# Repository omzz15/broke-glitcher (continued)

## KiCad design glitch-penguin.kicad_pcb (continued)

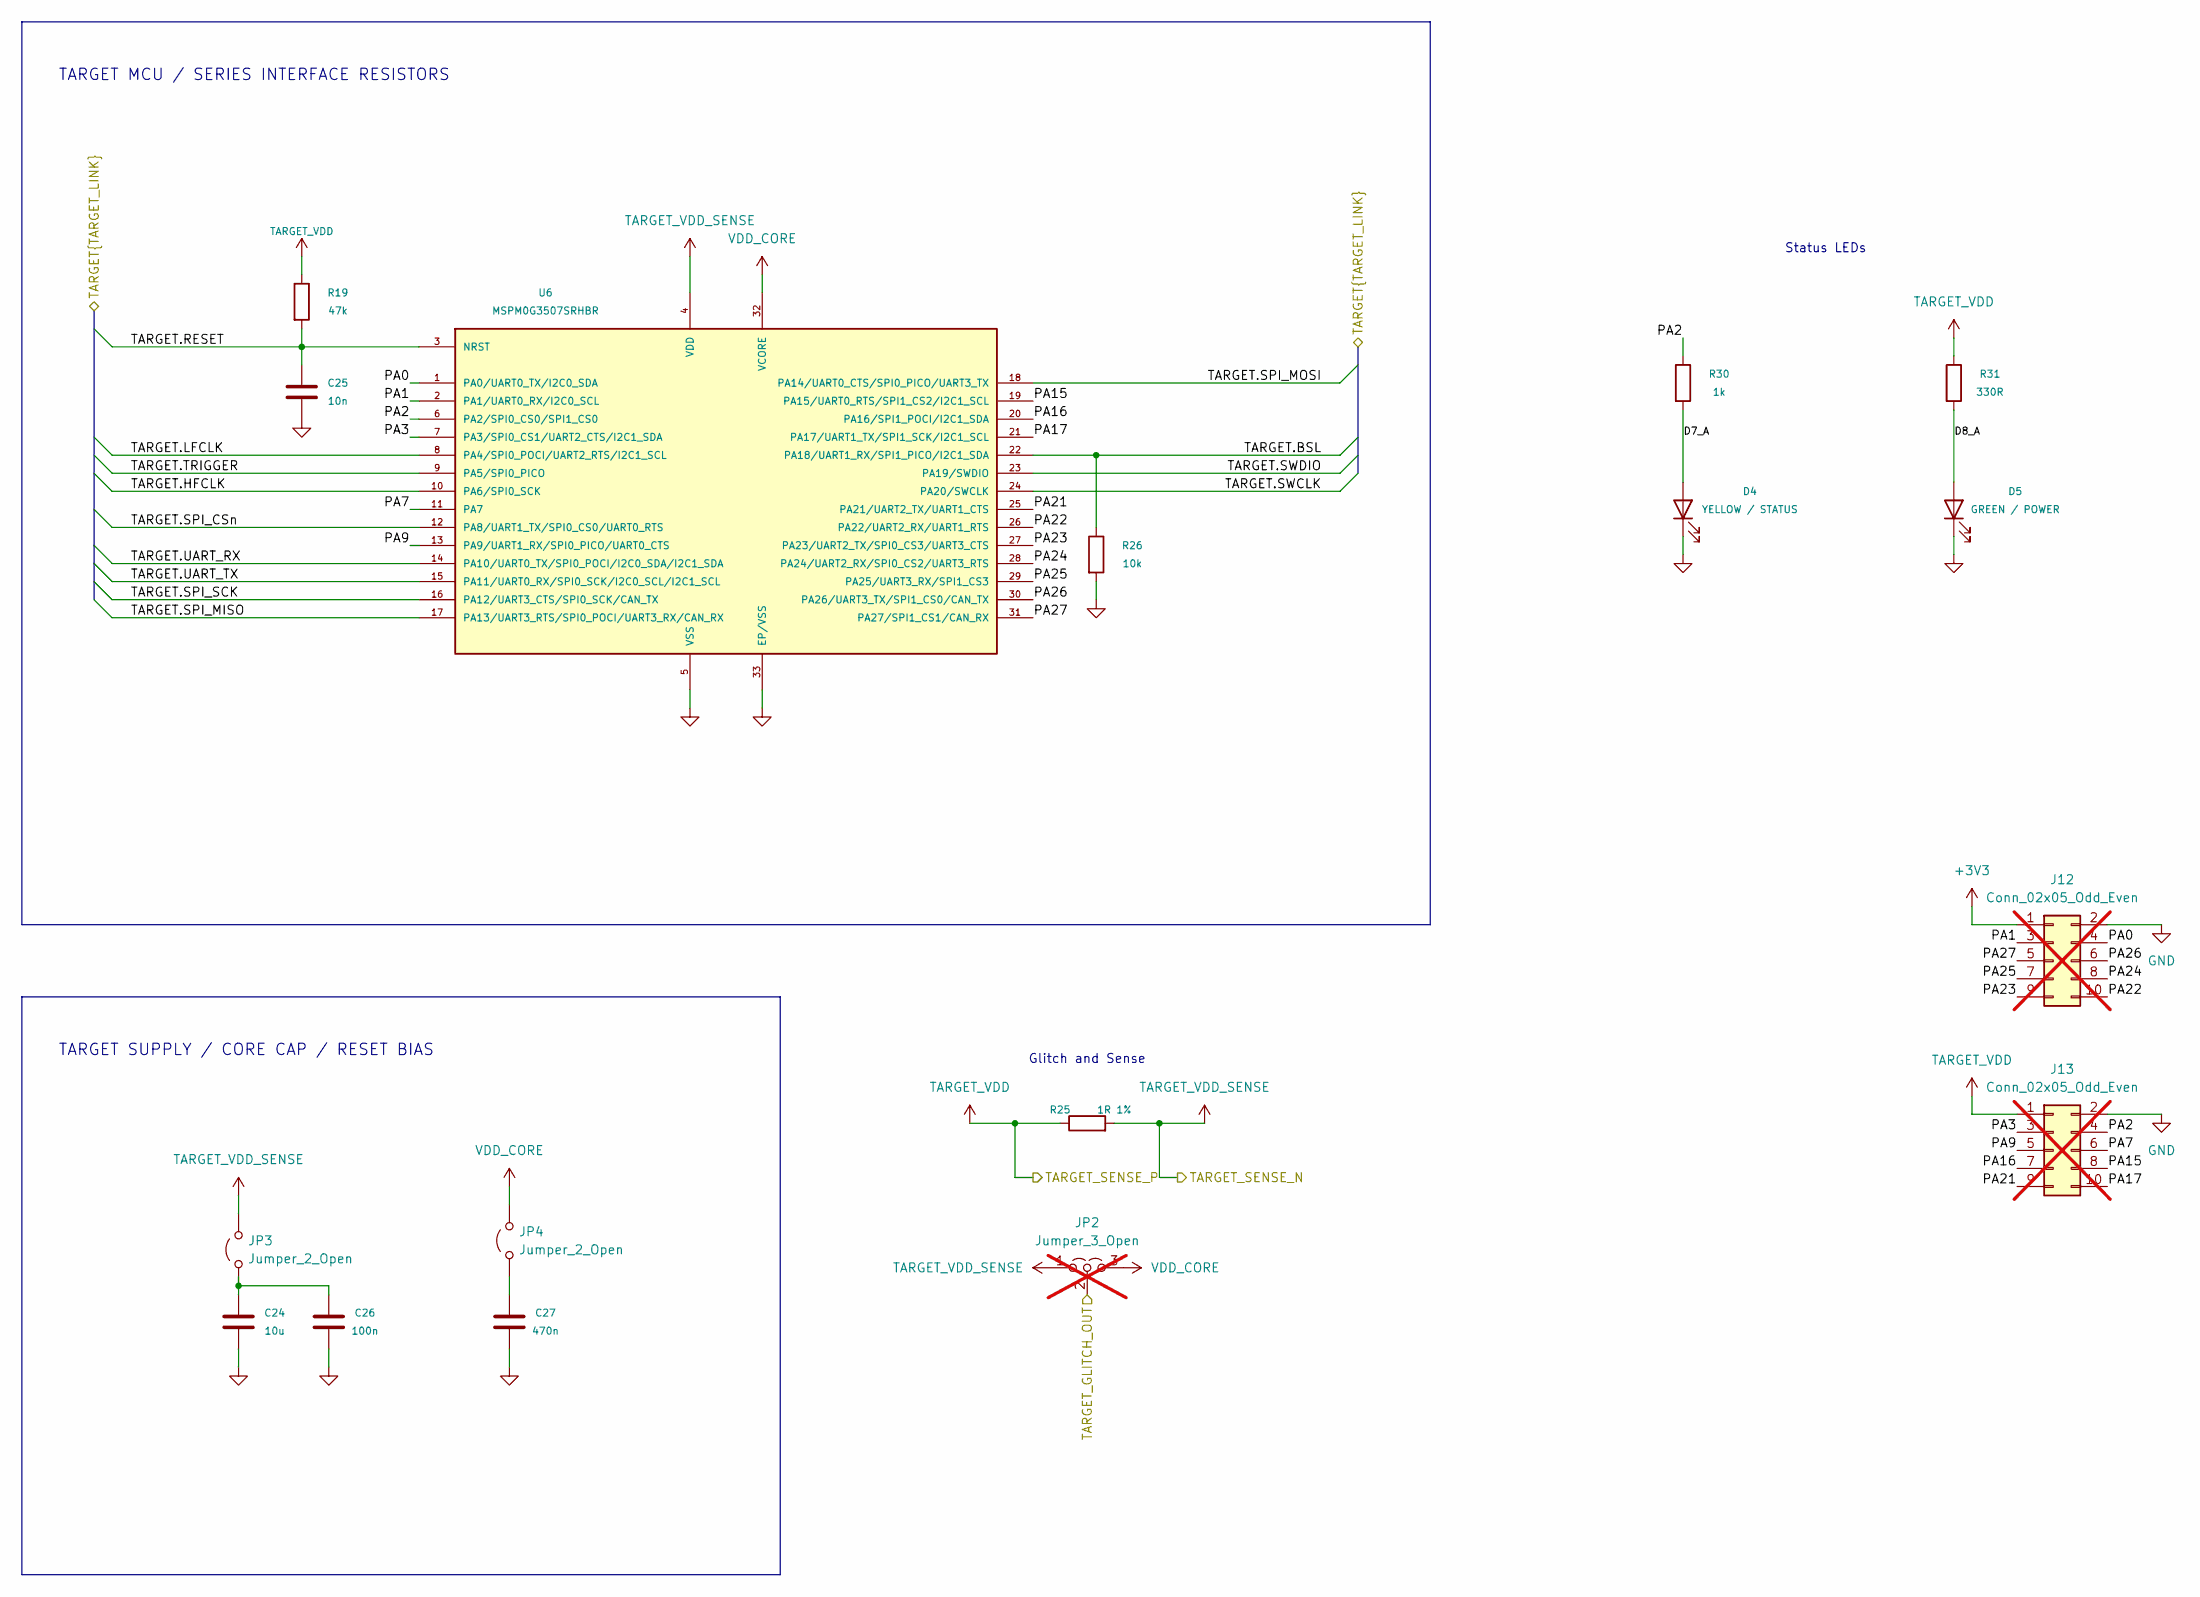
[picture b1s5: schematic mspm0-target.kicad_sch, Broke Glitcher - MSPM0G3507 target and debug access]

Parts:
C24: 10u; C_0805_2012Metric; MPN CL21A106KAYNNNE; LCSC Part # C15850
C25: 10n; C_0402_1005Metric; Tolerance ±10%; Voltage Rating 50 V; MPN CL05B103KB5NNNC; LCSC Part # C15195
C26: 100n; C_0402_1005Metric; Tolerance ±10%; Voltage Rating 16 V; MPN CL05B104KO5NNNC; LCSC Part # C1525
C27: 470n; C_0603_1608Metric; MPN CL10B474KA8NNNC; LCSC Part # C1623
D4: YELLOW / STATUS; LED_0603_1608Metric; MPN KT-0603Y; LCSC Part # C2287
D5: GREEN / POWER; LED_0603_1608Metric; MPN KT-0603G; LCSC Part # C12624
J12, J13: Conn_02x05_Odd_Even; PinHeader_2x05_P2.54mm_Vertical; not fitted
JP2: Jumper_3_Open; PinHeader_1x03_P2.54mm_Vertical; not fitted
JP3, JP4: Jumper_2_Open; SolderJumper-2_P1.3mm_Open_TrianglePad1.0x1.5mm
R19: 47k; R_0402_1005Metric; Tolerance ±1%; Voltage Rating 50 V; MPN 0402WGF4702TCE; LCSC Part # C25792
R25: 1R 1%; R_1206_3216Metric; MPN RC1206FR-071RL; LCSC Part # C137355
R26: 10k; R_0402_1005Metric; Tolerance ±1%; Voltage Rating 50 V; MPN 0402WGF1002TCE; LCSC Part # C25744
R30: 1k; R_0402_1005Metric; Tolerance ±1%; Voltage Rating 50 V; MPN 0402WGF1001TCE; LCSC Part # C11702
R31: 330R; R_0402_1005Metric; Tolerance ±1%; Voltage Rating 50 V; MPN 0402WGF3300TCE; LCSC Part # C25104
U6: MSPM0G3507SRHBR; Texas_RHB0032E_VQFN-32-1EP_5x5mm_P0.5mm_EP3.45x3.45mm_Therm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; MPN MSPM0G3507SRHBR; LCSC Part # C20618748

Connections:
+3V3: J12.1; also elsewhere on the board
/Breakaway interface/LINK_GPIO16: U6.17 (PA13/UART3_RTS/SPI0_POCI/UART3_RX/CAN_RX); also elsewhere on the board
/Breakaway interface/LINK_GPIO18: U6.16 (PA12/UART3_CTS/SPI0_SCK/CAN_TX); also elsewhere on the board
/Breakaway interface/LINK_GPIO19: U6.18 (PA14/UART0_CTS/SPI0_PICO/UART3_TX); also elsewhere on the board
/Breakaway interface/LINK_GPIO20: U6.15 (PA11/UART0_RX/SPI0_SCK/I2C0_SCL/I2C1_SCL); also elsewhere on the board
/Breakaway interface/LINK_GPIO21: U6.14 (PA10/UART0_TX/SPI0_POCI/I2C0_SDA/I2C1_S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); also elsewhere on the board
/Breakaway interface/LINK_GPIO22: U6.12 (PA8/UART1_TX/SPI0_CS0/UART0_RTS); also elsewhere on the board
/Breakaway interface/LINK_GPIO23: U6.10 (PA6/SPI0_SCK); also elsewhere on the board
/Breakaway interface/LINK_GPIO24: U6.9 (PA5/SPI0_PICO); also elsewhere on the board
/Breakaway interface/LINK_GPIO25: U6.8 (PA4/SPI0_POCI/UART2_RTS/I2C1_SCL); also elsewhere on the board
/Breakaway interface/LINK_GPIO26: C25.1, R19.2, U6.3 (NRST); also elsewhere on the board
/Breakaway interface/LINK_GPIO27: R26.1, U6.22 (PA18/UART1_RX/SPI1_PICO/I2C1_SDA); also elsewhere on the board
/Breakaway interface/LINK_GPIO28: U6.23 (PA19/SWDIO); also elsewhere on the board
/Breakaway interface/LINK_GPIO29: U6.24 (PA20/SWCLK); also elsewhere on the board
/Breakaway interface/TARGET_GLITCH_OUT: JP2.2 (C); also elsewhere on the board
/MSPM0G3507 target and debug access/D7_A: D4.2 (A), R30.2
/MSPM0G3507 target and debug access/D8_A: D5.2 (A), R31.2
/MSPM0G3507 target and debug access/PA0: J12.4, U6.1 (PA0/UART0_TX/I2C0_SDA)
/MSPM0G3507 target and debug access/PA1: J12.3, U6.2 (PA1/UART0_RX/I2C0_SCL)
/MSPM0G3507 target and debug access/PA2: J13.4, R30.1, U6.6 (PA2/SPI0_CS0/SPI1_CS0)
/MSPM0G3507 target and debug access/PA3: J13.3, U6.7 (PA3/SPI0_CS1/UART2_CTS/I2C1_SDA)
/MSPM0G3507 target and debug access/PA7: J13.6, U6.11 (PA7)
/MSPM0G3507 target and debug access/PA9: J13.5, U6.13 (PA9/UART1_RX/SPI0_PICO/UART0_CTS)
/MSPM0G3507 target and debug access/PA15: J13.8, U6.19 (PA15/UART0_RTS/SPI1_CS2/I2C1_SCL)
/MSPM0G3507 target and debug access/PA16: J13.7, U6.20 (PA16/SPI1_POCI/I2C1_SDA)
/MSPM0G3507 target and debug access/PA17: J13.10, U6.21 (PA17/UART1_TX/SPI1_SCK/I2C1_SCL)
/MSPM0G3507 target and debug access/PA21: J13.9, U6.25 (PA21/UART2_TX/UART1_CTS)
/MSPM0G3507 target and debug access/PA22: J12.10, U6.26 (PA22/UART2_RX/UART1_RTS)
/MSPM0G3507 target and debug access/PA23: J12.9, U6.27 (PA23/UART2_TX/SPI0_CS3/UART3_CTS)
/MSPM0G3507 target and debug access/PA24: J12.8, U6.28 (PA24/UART2_RX/SPI0_CS2/UART3_RTS)
/MSPM0G3507 target and debug access/PA25: J12.7, U6.29 (PA25/UART3_RX/SPI1_CS3)
/MSPM0G3507 target and debug access/PA26: J12.6, U6.30 (PA26/UART3_TX/SPI1_CS0/CAN_TX)
/MSPM0G3507 target and debug access/PA27: J12.5, U6.31 (PA27/SPI1_CS1/CAN_RX)
GND: C24.2, C25.2, C26.2, C27.2, D4.1 (K), D5.1 (K), J12.2, J13.2, R26.2, U6.5 (VSS), U6.33 (EP/VSS); also elsewhere on the board
unnamed: C24.1, C26.1, JP3.1 (A)
unnamed: C27.1, JP4.1 (A)
TARGET_VDD: J13.1, R19.1, R25.1, R31.1; also elsewhere on the board
TARGET_VDD_SENSE: JP2.1 (A), JP3.2 (B), R25.2, U6.4 (VDD); also elsewhere on the board
VDD_CORE: JP2.3 (B), JP4.2 (B), U6.32 (VCORE)

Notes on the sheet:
TARGET SUPPLY / CORE CAP / RESET BIAS
TARGET MCU / SERIES INTERFACE RESISTORS
Glitch and Sense
Status LEDs

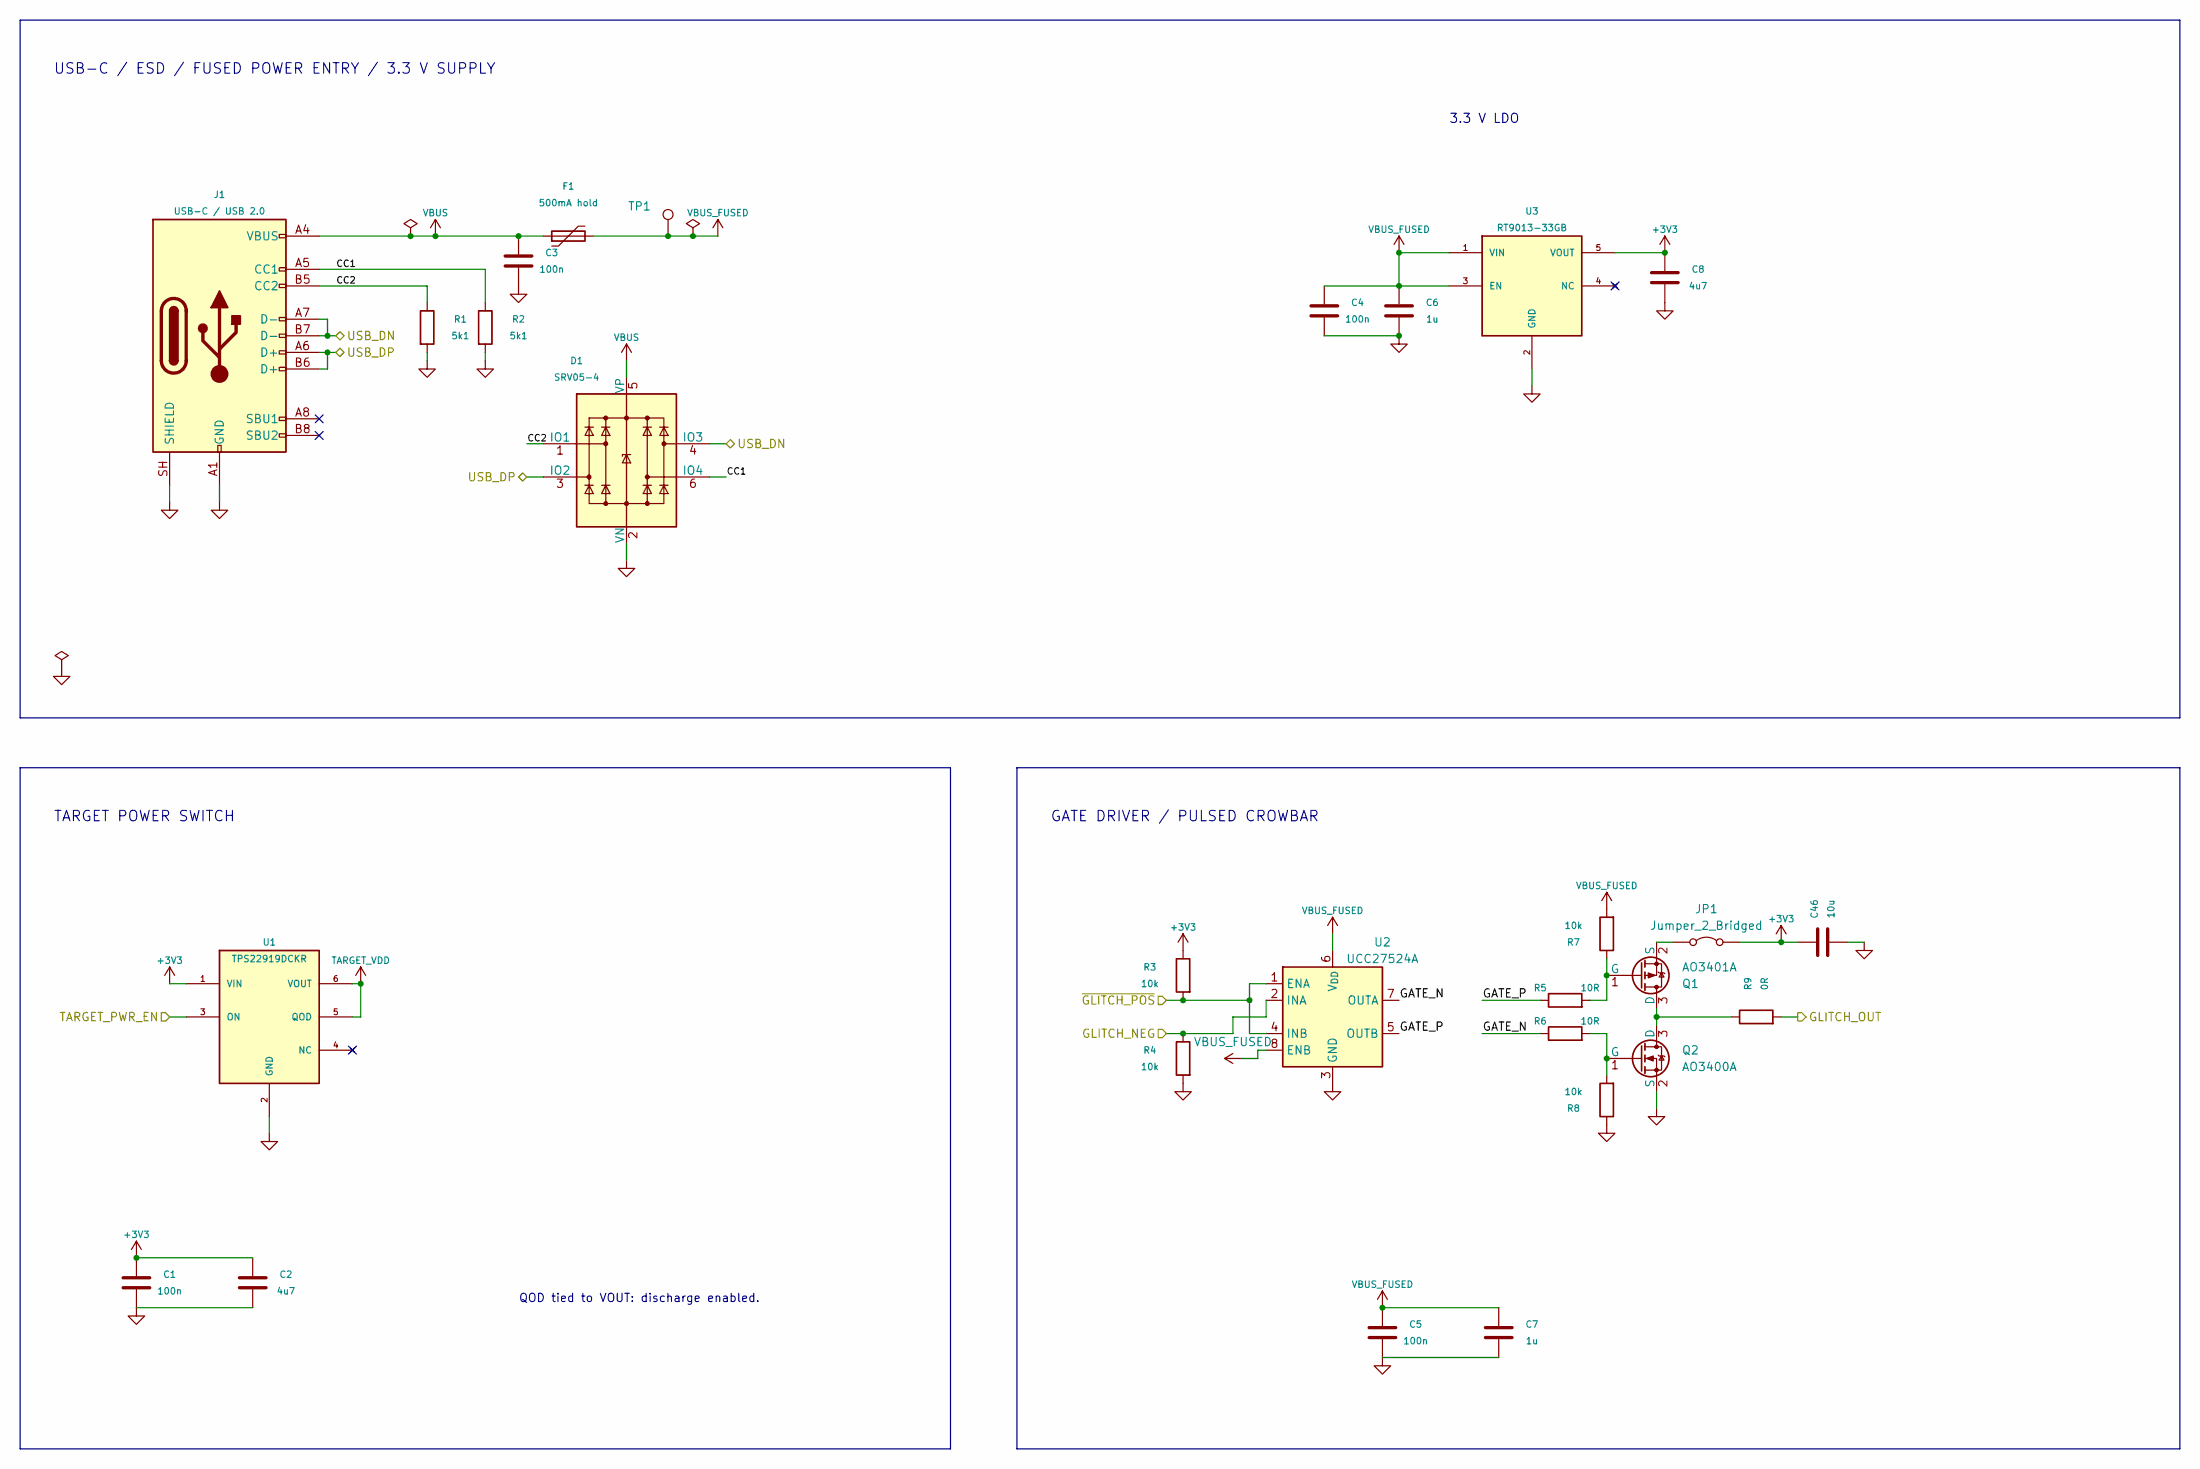
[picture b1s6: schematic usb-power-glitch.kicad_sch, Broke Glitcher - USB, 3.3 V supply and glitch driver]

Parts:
C1, C3, C4, C5: 100n; C_0402_1005Metric; Tolerance ±10%; Voltage Rating 16 V; MPN CL05B104KO5NNNC; LCSC Part # C1525
C2, C8: 4u7; C_0603_1608Metric; MPN CL10A475KP8NNNC; LCSC Part # C1705
C6, C7: 1u; C_0603_1608Metric; MPN CL10A105KB8NNNC; LCSC Part # C15849
C46: 10u; C_0805_2012Metric; MPN CL21A106KAYNNNE; LCSC Part # C15850
D1: SRV05-4; SOT-23-6; MPN SRV05-4; LCSC Part # C384887
F1: 500mA hold; Fuse_1206_3216Metric; MPN BSMD1206-050-30V; LCSC Part # C883126
J1: USB-C / USB 2.0; USB_C_Receptacle_HRO_TYPE-C-31-M-12; MPN TYPE-C-31-M-12; LCSC Part # C165948
JP1: Jumper_2_Bridged; SolderJumper-2_P1.3mm_Bridged_Pad1.0x1.5mm
Q1: AO3401A; SOT-23; MPN AO3401A; LCSC Part # C15127
Q2: AO3400A; SOT-23; MPN AO3400A; LCSC Part # C20917
R1, R2: 5k1; R_0402_1005Metric; Tolerance ±1%; Voltage Rating 50 V; MPN 0402WGF5101TCE; LCSC Part # C25905
R3, R4, R7, R8: 10k; R_0402_1005Metric; Tolerance ±1%; Voltage Rating 50 V; MPN 0402WGF1002TCE; LCSC Part # C25744
R5, R6: 10R; R_0603_1608Metric; MPN 0603WAF100JT5E; LCSC Part # C22859
R9: 0R; R_0603_1608Metric; MPN 0603WAF0000T5E; LCSC Part # C21189
TP1: TestPoint; TestPoint_Pad_D1.0mm
U1: TPS22919DCKR; SOT-363_SC-70-6; MPN TPS22919DCKR; LCSC Part # C2149796
U2: UCC27524A; SOIC-8_3.9x4.9mm_P1.27mm; MPN UCC27524ADR; LCSC Part # C185857
U3: RT9013-33GB; SOT-23-5; MPN RT9013-33GB; LCSC Part # C47773

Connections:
+3V3: C1.1, C2.1, C8.1, C46.1, JP1.2 (B), R3.1, U1.1 (VIN), U3.5 (VOUT); also elsewhere on the board
/GLITCH_OUT: R9.2; also elsewhere on the board
/RP2040 controller, flash and oscillator/GLITCH_NEG: R4.1, U2.2 (INA); also elsewhere on the board
/RP2040 controller, flash and oscillator/TARGET_PWR_EN: U1.3 (ON); also elsewhere on the board
/RP2040 controller, flash and oscillator/USB_DN: D1.4 (IO3), J1.A7 (D-), J1.B7 (D-); also elsewhere on the board
/RP2040 controller, flash and oscillator/USB_DP: D1.3 (IO2), J1.A6 (D+), J1.B6 (D+); also elsewhere on the board
/RP2040 controller, flash and oscillator/~GLITCH_POS: R3.2, U2.1 (ENA), U2.4 (INB); also elsewhere on the board
/USB, 3.3 V supply and glitch driver/CC1: D1.6 (IO4), J1.A5 (CC1), R2.1
/USB, 3.3 V supply and glitch driver/CC2: D1.1 (IO1), J1.B5 (CC2), R1.1
/USB, 3.3 V supply and glitch driver/GATE_N: R6.1, U2.7 (OUTA)
/USB, 3.3 V supply and glitch driver/GATE_P: R5.1, U2.5 (OUTB)
GND: C1.2, C2.2, C3.2, C4.2, C5.2, C6.2, C7.2, C8.2, C46.2, D1.2 (VN), J1.A1 (GND), J1.A12 (GND), J1.B1 (GND), J1.B12 (GND), J1.SH (SHIELD), Q2.2 (S), R1.2, R2.2, R4.2, R8.1, U1.2 (GND), U2.3 (GND), U3.2 (GND); also elsewhere on the board
unnamed: JP1.1 (A), Q1.2 (S)
unnamed: Q1.3 (D), Q2.3 (D), R9.1
unnamed: Q1.1 (G), R5.2, R7.1
unnamed: Q2.1 (G), R6.2, R8.2
TARGET_VDD: U1.5 (QOD), U1.6 (VOUT); also elsewhere on the board
VBUS: C3.1, D1.5 (VP), F1.1, J1.A4 (VBUS), J1.A9 (VBUS), J1.B4 (VBUS), J1.B9 (VBUS)
VBUS_FUSED: C4.1, C5.1, C6.1, C7.1, F1.2, R7.2, TP1.1 (1_1), U2.6 (V_{DD}), U2.8 (ENB), U3.1 (VIN), U3.3 (EN)

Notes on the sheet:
USB-C / ESD / FUSED POWER ENTRY / 3.3 V SUPPLY
GATE DRIVER / PULSED CROWBAR
3.3 V LDO
TARGET POWER SWITCH
QOD tied to VOUT: discharge enabled.

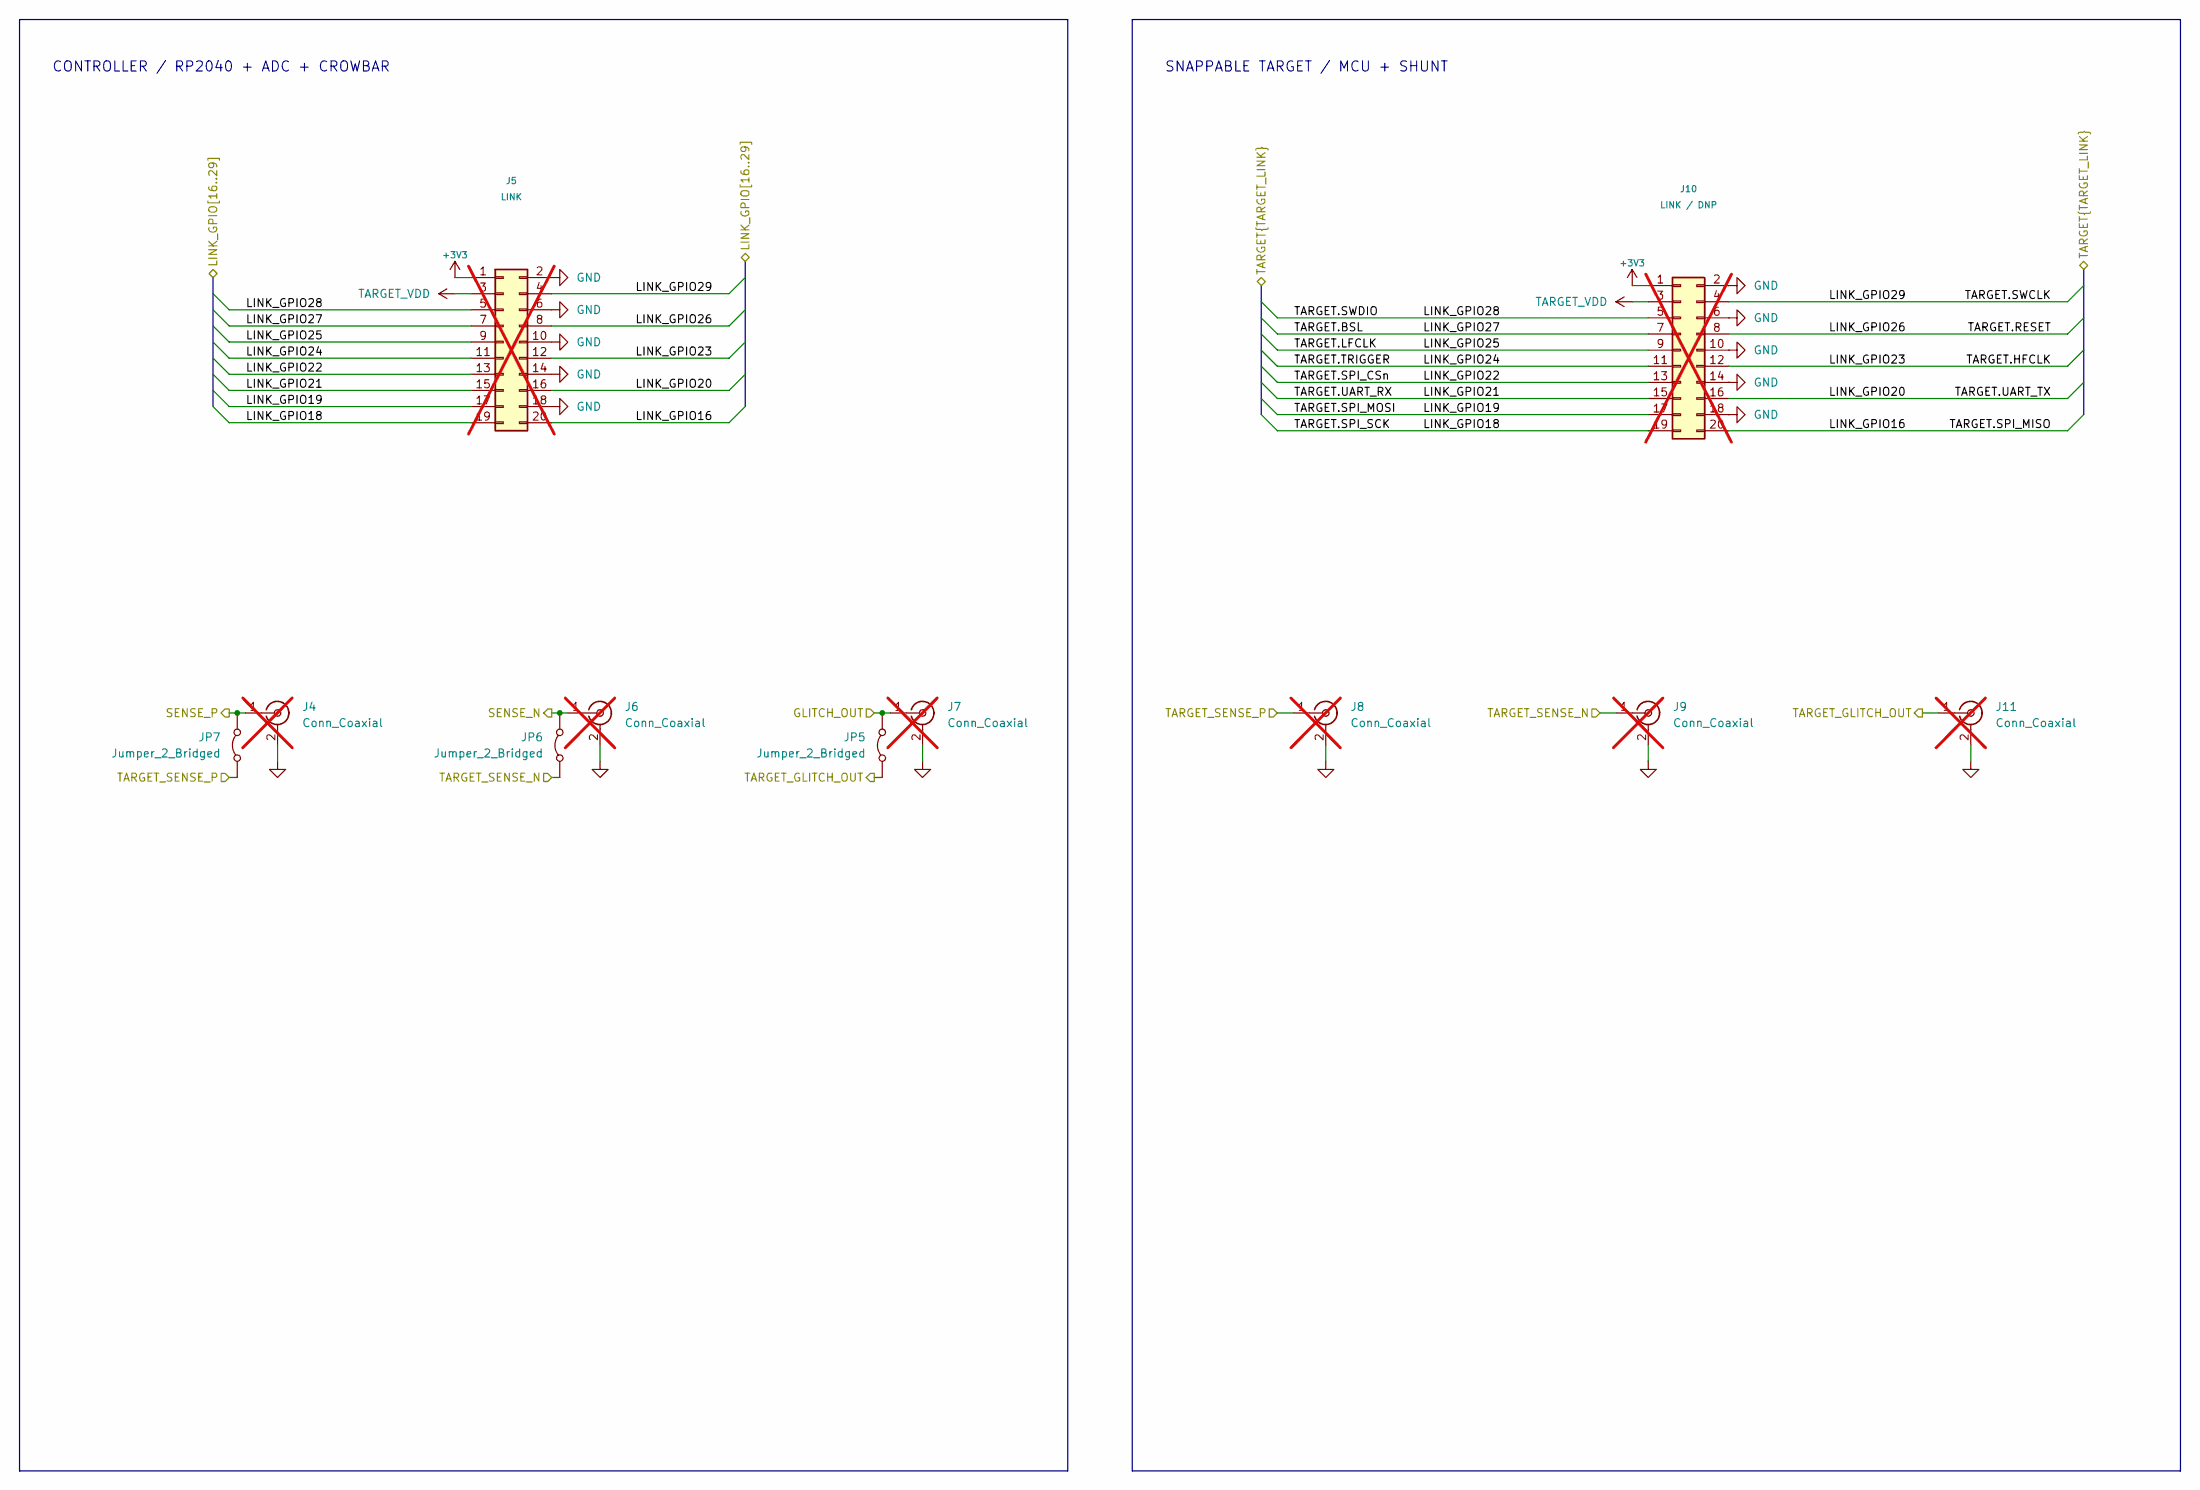
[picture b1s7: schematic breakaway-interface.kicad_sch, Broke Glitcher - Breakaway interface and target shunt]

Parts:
J4, J6, J7, J8, J9, J11: Conn_Coaxial; SMA_Molex_73251-1153_EdgeMount_Horizontal; not fitted
J5: LINK; PinHeader_2x10_P2.54mm_Vertical; not fitted
J10: LINK / DNP; PinHeader_2x10_P2.54mm_Vertical; not fitted
JP5, JP6, JP7: Jumper_2_Bridged; SolderJumper-2_P1.3mm_Bridged_Pad1.0x1.5mm

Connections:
+3V3: J5.1, J10.1; also elsewhere on the board
/AC current-shunt amplifier/SENSE_N: J6.1 (In), JP6.1 (A); also elsewhere on the board
/AC current-shunt amplifier/SENSE_P: J4.1 (In), JP7.1 (A); also elsewhere on the board
/Breakaway interface/LINK_GPIO16: J5.20, J10.20; also elsewhere on the board
/Breakaway interface/LINK_GPIO18: J5.19, J10.19; also elsewhere on the board
/Breakaway interface/LINK_GPIO19: J5.17, J10.17; also elsewhere on the board
/Breakaway interface/LINK_GPIO20: J5.16, J10.16; also elsewhere on the board
/Breakaway interface/LINK_GPIO21: J5.15, J10.15; also elsewhere on the board
/Breakaway interface/LINK_GPIO22: J5.13, J10.13; also elsewhere on the board
/Breakaway interface/LINK_GPIO23: J5.12, J10.12; also elsewhere on the board
/Breakaway interface/LINK_GPIO24: J5.11, J10.11; also elsewhere on the board
/Breakaway interface/LINK_GPIO25: J5.9, J10.9; also elsewhere on the board
/Breakaway interface/LINK_GPIO26: J5.8, J10.8; also elsewhere on the board
/Breakaway interface/LINK_GPIO27: J5.7, J10.7; also elsewhere on the board
/Breakaway interface/LINK_GPIO28: J5.5, J10.5; also elsewhere on the board
/Breakaway interface/LINK_GPIO29: J5.4, J10.4; also elsewhere on the board
/Breakaway interface/TARGET_GLITCH_OUT: J11.1 (In), JP5.2 (B); also elsewhere on the board
/GLITCH_OUT: J7.1 (In), JP5.1 (A); also elsewhere on the board
GND: J4.2 (Ext), J5.2, J5.6, J5.10, J5.14, J5.18, J6.2 (Ext), J7.2 (Ext), J8.2 (Ext), J9.2 (Ext), J10.2, J10.6, J10.10, J10.14, J10.18, J11.2 (Ext); also elsewhere on the board
TARGET_VDD: J5.3, J8.1 (In), J10.3, JP7.2 (B); also elsewhere on the board
TARGET_VDD_SENSE: J9.1 (In), JP6.2 (B); also elsewhere on the board

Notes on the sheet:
SNAPPABLE TARGET / MCU + SHUNT
CONTROLLER / RP2040 + ADC + CROWBAR

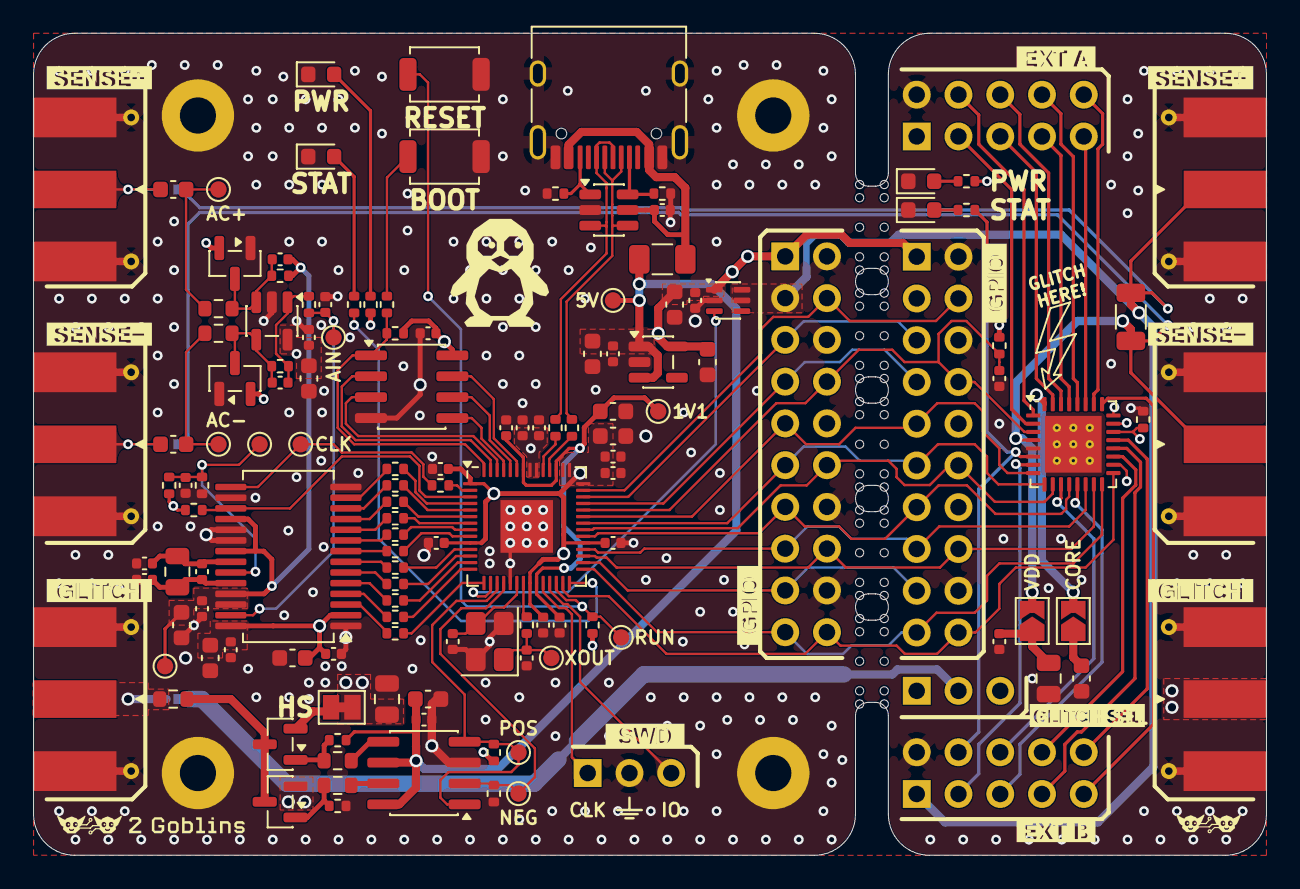
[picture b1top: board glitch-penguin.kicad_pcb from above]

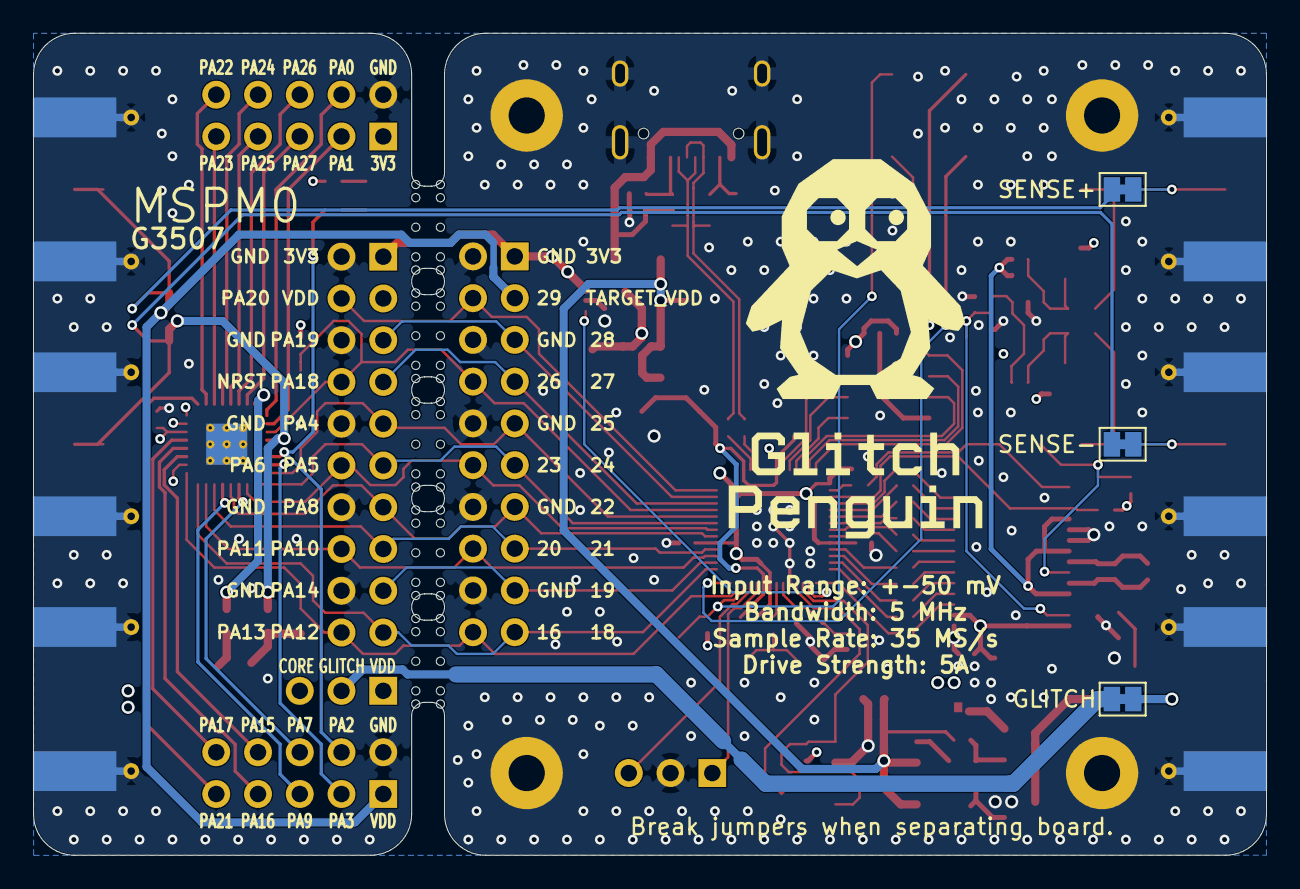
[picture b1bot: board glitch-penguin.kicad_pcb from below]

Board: 4 copper layers, 75.0 x 50.0 mm, 145 parts (3 on the bottom side), 111 nets.

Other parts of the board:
MB1: MouseBite_Seam_2x45mm_5Tabs5mm_D0.5_Route

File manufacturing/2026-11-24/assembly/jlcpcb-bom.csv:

Comment,Designator,Footprint,LCSC Part #,Quantity,Manufacturer Part Number
100n,"C1,C3,C4,C5,C9,C10,C11,C12,C13,C15,C16,C17,C18,C19,C22,C26,C28,C29,C31,C32,C33,C35,C37,C44",C_0402_1005Metric,C1525,24,CL05B104KO5NNNC
4u7,"C2,C8,C38,C45",C_0603_1608Metric,C1705,4,CL10A475KP8NNNC
1u,"C6,C7,C14,C20,C30,C36,C39,C40",C_0603_1608Metric,C15849,8,CL10A105KB8NNNC
33p,"C21,C23,C43",C_0402_1005Metric,C1562,3,0402CG330J500NT
10u,"C24,C34,C46",C_0805_2012Metric,C15850,3,CL21A106KAYNNNE
10n,C25,C_0402_1005Metric,C15195,1,CL05B103KB5NNNC
470n,C27,C_0603_1608Metric,C1623,1,CL10B474KA8NNNC
7p5,"C41,C42",C_0402_1005Metric,C43514,2,0402CG7R5C500NT
SRV05-4,D1,SOT-23-6,C384887,1,SRV05-4
GREEN / POWER,"D2,D5",LED_0603_1608Metric,C12624,2,KT-0603G
YELLOW / STATUS,"D3,D4",LED_0603_1608Metric,C2287,2,KT-0603Y
"BAT754S,215","D6,D7",SOT-23,C426771,2,"BAT754S,215"
500mA hold,F1,Fuse_1206_3216Metric,C883126,1,BSMD1206-050-30V
USB-C / USB 2.0,J1,USB_C_Receptacle_HRO_TYPE-C-31-M-12,C165948,1,TYPE-C-31-M-12
AO3401A,Q1,SOT-23,C15127,1,AO3401A
AO3400A,Q2,SOT-23,C20917,1,AO3400A
5k1,"R1,R2",R_0402_1005Metric,C25905,2,0402WGF5101TCE
10k,"R3,R4,R7,R8,R10,R15,R26,R32,R33,R34",R_0402_1005Metric,C25744,10,0402WGF1002TCE
10R,"R5,R6",R_0603_1608Metric,C22859,2,0603WAF100JT5E
0R,R9,R_0603_1608Metric,C21189,1,0603WAF0000T5E
27R,"R11,R12,R13,R35,R36,R37,R38,R39,R40,R41,R42,R43,R44,R45,R50",R_0402_1005Metric,C25100,15,0402WGF270JTCE
330R,"R14,R17,R31",R_0402_1005Metric,C25104,3,0402WGF3300TCE
1k,"R16,R18,R30",R_0402_1005Metric,C11702,3,0402WGF1001TCE
47k,R19,R_0402_1005Metric,C25792,1,0402WGF4702TCE
1R 1%,R25,R_1206_3216Metric,C137355,1,RC1206FR-071RL
200R 0.1%,"R46,R47",R_0603_1608Metric,C2989022,2,TC0325B2000T5F
2k 0.1%,"R48,R49",R_0402_1005Metric,C852711,2,RT0402BRD072KL
BOOTSEL / RP2040 RESET,"SW1,SW2",SW_SPST_TS-1088-xR020,C720477,2,TS-1088-AR02016
TPS22919DCKR,U1,SOT-363_SC-70-6,C2149796,1,TPS22919DCKR
UCC27524A,U2,SOIC-8_3.9x4.9mm_P1.27mm,C185857,1,UCC27524ADR
RT9013-33GB,U3,SOT-23-5,C47773,1,RT9013-33GB
RP2040,U4,QFN-56-1EP_7x7mm_P0.4mm_EP3.2x3.2mm,C2040,1,RP2040
P25Q16SH-SSH-IR,U5,SOIC-8_3.9x4.9mm_P1.27mm,C7466814,1,P25Q16SH-SSH-IR
MSPM0G3507SRHBR,U6,Texas_RHB0032E_VQFN-32-1EP_5x5mm_P0.5mm_EP3.45x3.45mm_ThermalVias,C20618748,1,MSPM0G3507SRHBR
MS9280,U7,SSOP-28_5.3x10.2mm_P0.65mm,C1509021,1,MS9280
SGM8051,U8,SOT-23-5,C5122371,1,SGM8051XN5/TR
12MHz / CL20pF,Y1,Crystal_SMD_3225-4Pin_3.2x2.5mm,C9002,1,X322512MSB4SI
